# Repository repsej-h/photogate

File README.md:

# Photogate

## Project description

The photogate project is an Arduino compatible PCB, designed to take precise measurements of for example a pendulum's period or the speed of a miniature car in a test rig. Since the photogate project is driven by a school project, some screenshots and component workings will be included in this repository.

### The PCB

The U-shaped PCB most importantly features a 3 pin connector. From left to right the pins need to be connected to `GND`, `digital interrupt` & `+5V` on your Arduino. There are two mounting holes in the PCB, which could be used to attach the photogate to a 3d printed mounting piece (which is not yet developed). Last every PCB features a unique QR-code, for easy identification of the PCB's

A screenshot of the schematics can by found in the `references` folder

### Components

Only 5 components are placed on the PCB. Starting off with `R1` and `R2`, these are 220 $\Omega$ and 2000 $\Omega$ resistors respectively. These are placed on the board as 0805 SMD **resistors**. Next is a 3 pin connector with a 90 degree bend, making the photogate easily compatible with a breadboard. Alternatively, when mounting the PCB, female to male Arduino jumper wires can be used. Next we have the more vital components. The first one is the 940 nm LED, which constantly emits light when connected to a power source. Finally a 940 nm `insert type`phototransistor either blocks or allows electricity to flow through the circuit. This flow triggers an interrupt request (IRQ)

## Sponsership

Special thanks to [PCBWay](https://www.pcbway.com/) for providing me with quick and easy pcb prototyping! 

Working with them has been nothing but smooth. Their boards are top-notch, their turnaround times are fast, and the entire process is incredibly easy from start to finish. Whether you're prototyping something new or scaling up for production, they make sure you get exactly what you need — quickly and reliably.

If you are interested in ordering some photogates, I highly recommend checking them out via [this link](https://www.pcbway.com/project/shareproject/Arduino_Photogate_PCB_ff1ebb34.html).

# Scripts

Currently the photogate project features 3 scripts:

## photogate.ino

This script uses a single photogate pcb to measure the time between two triggers.
For demonstration purposes, the internal arduino led is turned on in between the start and stop trigger.
A picture of the hardware setup is presented below. In order for the interrupt to work, the `SensorPin` **has to be wired** to the `digital 2 / 3` pin on an Arduino Uno. (cfr interrupts)

## photogate_pendulum.ino

This script is used to measure the period of a pendulum using a single photogate. It calculates the high-precision average of 10 measured periods to ensure experimental accuracy.

### Key Features

- **Automatic Data Reset:** The script features an sanity check. If the interval between triggers exceeds **5 seconds** (5000 ms), the script assumes the experiment has been paused or adjusted. It will automatically discard previous partial measurements and restart the count from zero.

- **Smooth Table Output:** Data is printed to the Serial Monitor in a strictly aligned table format. This includes:
  
  - **Time:** Padded numerical values to prevent column shifting.
  
  - **Progress Bar:** A visual representation of how many readings are left before the average is calculated.

### Hardware Setup

In order for the timing interrupt to work correctly, the **SensorPin** must be wired to a pin capable of handeling interrupts.

- **Arduino Uno:** Connect to **Digital Pin 2** or **Digital Pin 3**.

### How to Use

1. Connect the hardware as described above.

2. Upload the script and open the **Serial Monitor** (set to **9600 Baud**).

3. Release the pendulum. The first pass will initialize the timer.

4. The table will populate automatically. If you stop the pendulum for more than 5 seconds, the table will reset itself for your next trial.

5. After 10 periods, the final average (T×2) will be displayed in a result block.

## SlingerPeriode.ino

This script has the same functionality as the `photogate_pendulum.ino` script, but has been modified to be used on a college information day. Most important changes are reformatting the script's output and adding instructions for the demo in de code documentation. Also, this script is based on a older version of the pendulum script and still uses analog readings. Theirfore connect the `SensorPin` to pin `A0`!

## speed_measurement.ino

This script is designed to calculate the speed of an object traveling through multiple photogates. Unlike previous projects, an array of photogates is used to collect timestamps along the path of the object. This data is used to calculate the speed of the object for each interval.

> [!NOTE]
> Since old Arduino Uno's only feature 2 interupt pins, only 2 photogates can be used. Please consult [Arduino docs](https://docs.arduino.cc/language-reference/en/functions/external-interrupts/attachInterrupt/) to check if your Arduino model can support more than 2 interrupts.

### Configure the script

By default the script is configured to work with two photogates, connected to digital pins `2` & `3`.  In this case, simply input the distance in cm between the 2 gates right here: `unsigned int distances[pinsLength - 1] = {100};`

When adding more photogates, first add your pins into the `int pins[]` seperatedby comma's. Next plug in the distances between the gates, also separated by comma's into `unsigned int distances[pinsLength - 1]` and you are good to go. 

Until now the script has been tested with up to 3 photogates. Also note that the script doesn't bother in which order gates get triggered. This means that a set up can be used in both directions. The end user needs to interpret which is gate one, two, etc based on the object's trajectory.

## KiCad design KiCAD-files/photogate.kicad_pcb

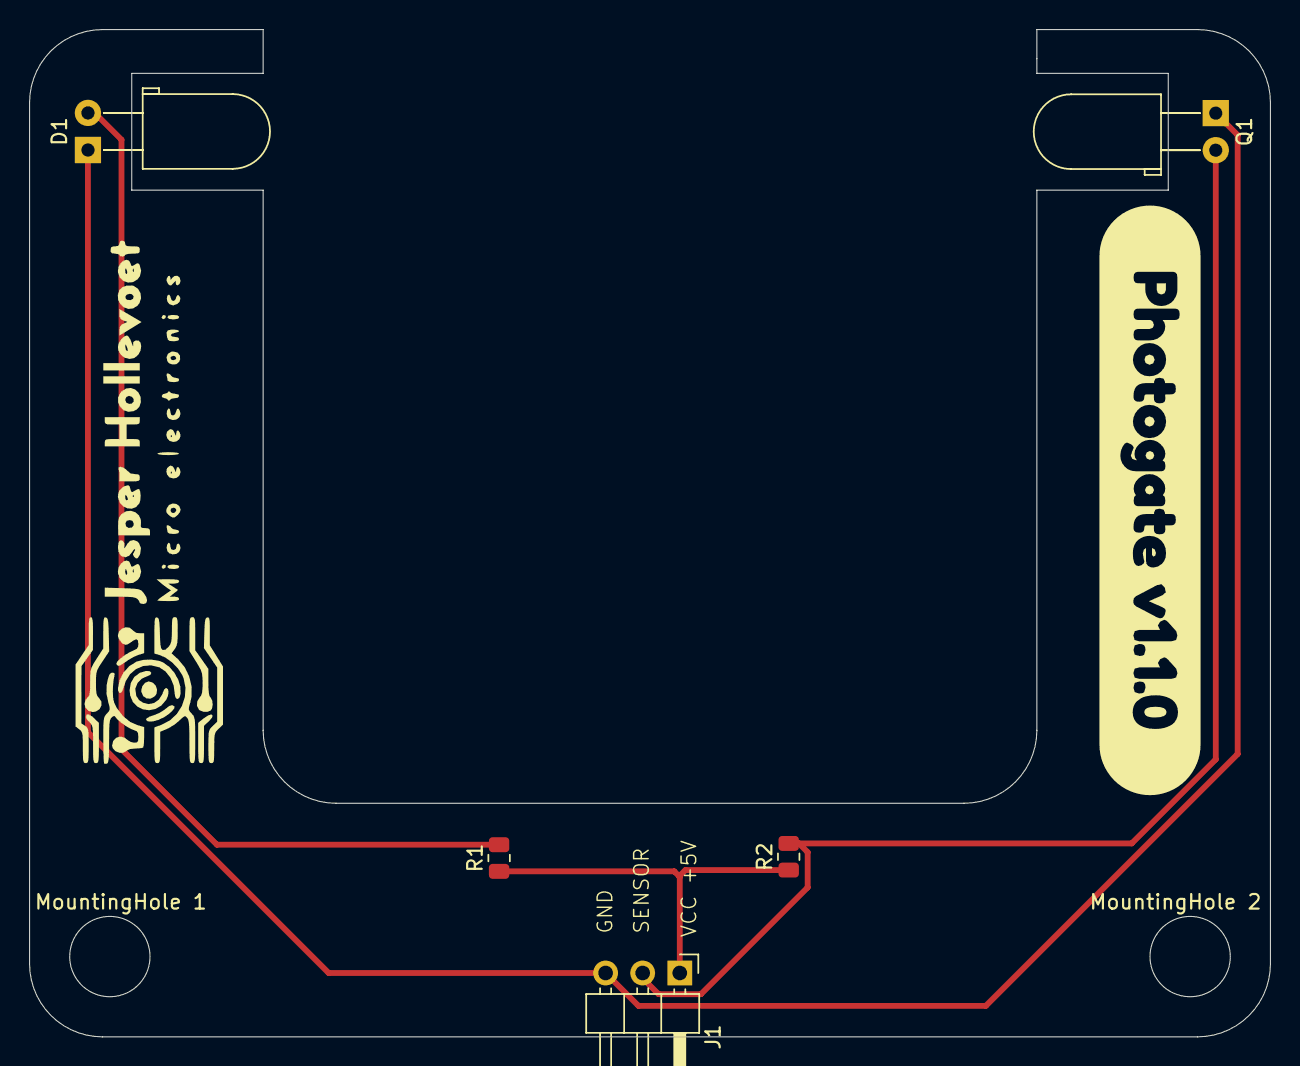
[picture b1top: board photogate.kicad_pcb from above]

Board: 2 copper layers, 85.0 x 69.0 mm, 8 parts (0 on the bottom side), 4 nets.

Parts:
D1: IR26-21C_L110_TR8; LED_D5.0mm_Horizontal_O3.81mm_Z3.0mm
J1: Conn_01x03_Pin; PinHeader_1x03_P2.54mm_Horizontal
MountingHole 1, MountingHole 2: MountingHole; MountingHole_5.5mm
Q1: Q1; LED_D5.0mm_Horizontal_O3.81mm_Z3.0mm
R1: 220; R_0805_2012Metric
R2: 2k; R_0805_2012Metric
kibuzzard-67ED3B28: G***; kibuzzard-67ED3B28

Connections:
/gnd: D1.1 (K), J1.3, Q1.1
/sensor: J1.2, Q1.2, R2.2
/vcc: J1.1, R1.1, R2.1
unnamed: D1.2 (A), R1.2

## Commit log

2025-04-02 V1 final touches
2025-04-02 adding revision so kicad export script works
2025-04-24 Moving KiCAD files to folder & adding scripts folder
2025-04-24 Create README.md
    initial version of documentation
2025-04-24 update documentation to include scripts discription
2025-04-24 Add pictures to README.md
2025-04-24 update photo format
2025-04-25 add project and pcb description
2025-04-25 typo fix
2025-04-25 include components in readme and init the references folder
2025-04-25 typo fixes
2025-04-27 Adding the initial version of the demo-day script
2025-04-27 Cleaning up the script
2025-04-27 Adjust period calculation
2025-04-27 fix periods array declaration
2025-05-30 implementation of interrupt
2025-05-30 remove unnecessary code
2025-05-30 closing #2, updating documentation
2025-06-30 remove unnecessary documentation
2025-06-30 initial version with 2 photogates
2025-06-30 Update `void setup` to easily accommodate more photogates
2025-07-01 update void loop to accommodate multiple photo gates
2025-07-01 include speed measurements script description
2025-07-01 add manual for speed_measurement script.
2025-07-01 addition of scripts working and user interpretation
2025-07-05 addition of render
2025-07-07 replace static shot by video
2025-07-07 update documentation for demo script
2025-07-07 replace outdate info about scripts working
2025-07-07 addition of some references and production files
2025-07-27 add message of sponser
2025-07-28 add sponsor's logo
2025-07-28 consistency fix
2025-08-06 Visuel improvement
2026-04-07 add auto reset
2026-04-07 format cli output
2026-04-07 print tabel header before each new measurement
2026-04-07 Adapt closing of #1
